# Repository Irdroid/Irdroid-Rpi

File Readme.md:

# Irdroid-Rpi Infrared Transceiver for Raspberry Pi

The latest gadget that we are working on is the Irdroid-Rpi Infrared Transceiver HAT / Add-on board for Raspberry Pi. The board provides Infrared Transmitter , Infrared Receiver and UEXT interconnect for Olimex sensors and boards designed with the UEXT connector. The board can be stacked on top of the Rpi board and you could turn your Rpi into a fully functional Infrared remote control for you home infrared consumer electronics. The Irdroid-Rpi is compatible with the LIRC/ Lirc GPIO driver for raspberry Pi and the LIRC utilities for recording and transmitting infrared signals can be used. The Irdroid-Rpi uses a optical IR amplification technique that allows to transmit high power IR signal by signal amplification after the IR light is emitted.

- Infrared Transceiver add-on / HAT for Raspberry Pi
- Infrared Transmitter @940nm with 10+ meters range
- Infrared Receiver up to 40khz and 10+ meters of receive range
- On-board UEXT Interconnect for connecting Olimex sensors and boards.
- Open Source Hardware.

### Version
1.0

### Installation Instructions

Detailed Installation Instructions https://irdroid.eu/wp-content/uploads/2020/03/Irdroid-Rpi-Installation-Guide.txt

### Grab a sample

You can grab a sample board from http://www.irdroid.eu/irdroid-rpi-infrared-transceiver-raspberry-pi/
### Tech

The Irdroid-Rpi infrared transceiver for Raspberry Pi is also designed with the possibility to connect sensors and boards from Olimex (http://www.olimex.com) by using the on-board UEXT connector, designed by Olimex. You can check here what sensors are supported https://www.olimex.com/Products/Components/Sensors/ .

### Todos

 - Add holders for the infrared leds in schematic
 
### Updates

Irdroid-Rpi now has a DT Overlay support via the on-board eeprom that now ships with every board. Once attached to a Raspberry Pi, the Irdroid-Rpi Hat will be recognized automatically, it will set the board inputs and outputs, and it will load the appropriate Kernel LIRC-RPI drivers. This feature improoves user experience and it provides plug-n-play support for the Product. The user will only have to install lircd (if not shipped by default with the distribution used).

The Irdroid-Rpi board details such as Vendor and Product IDs are available in 

/proc/device-tree/hat

To query Product & Vendor use:

$ more product  

$ more vendor

License
----
GPL 2.0

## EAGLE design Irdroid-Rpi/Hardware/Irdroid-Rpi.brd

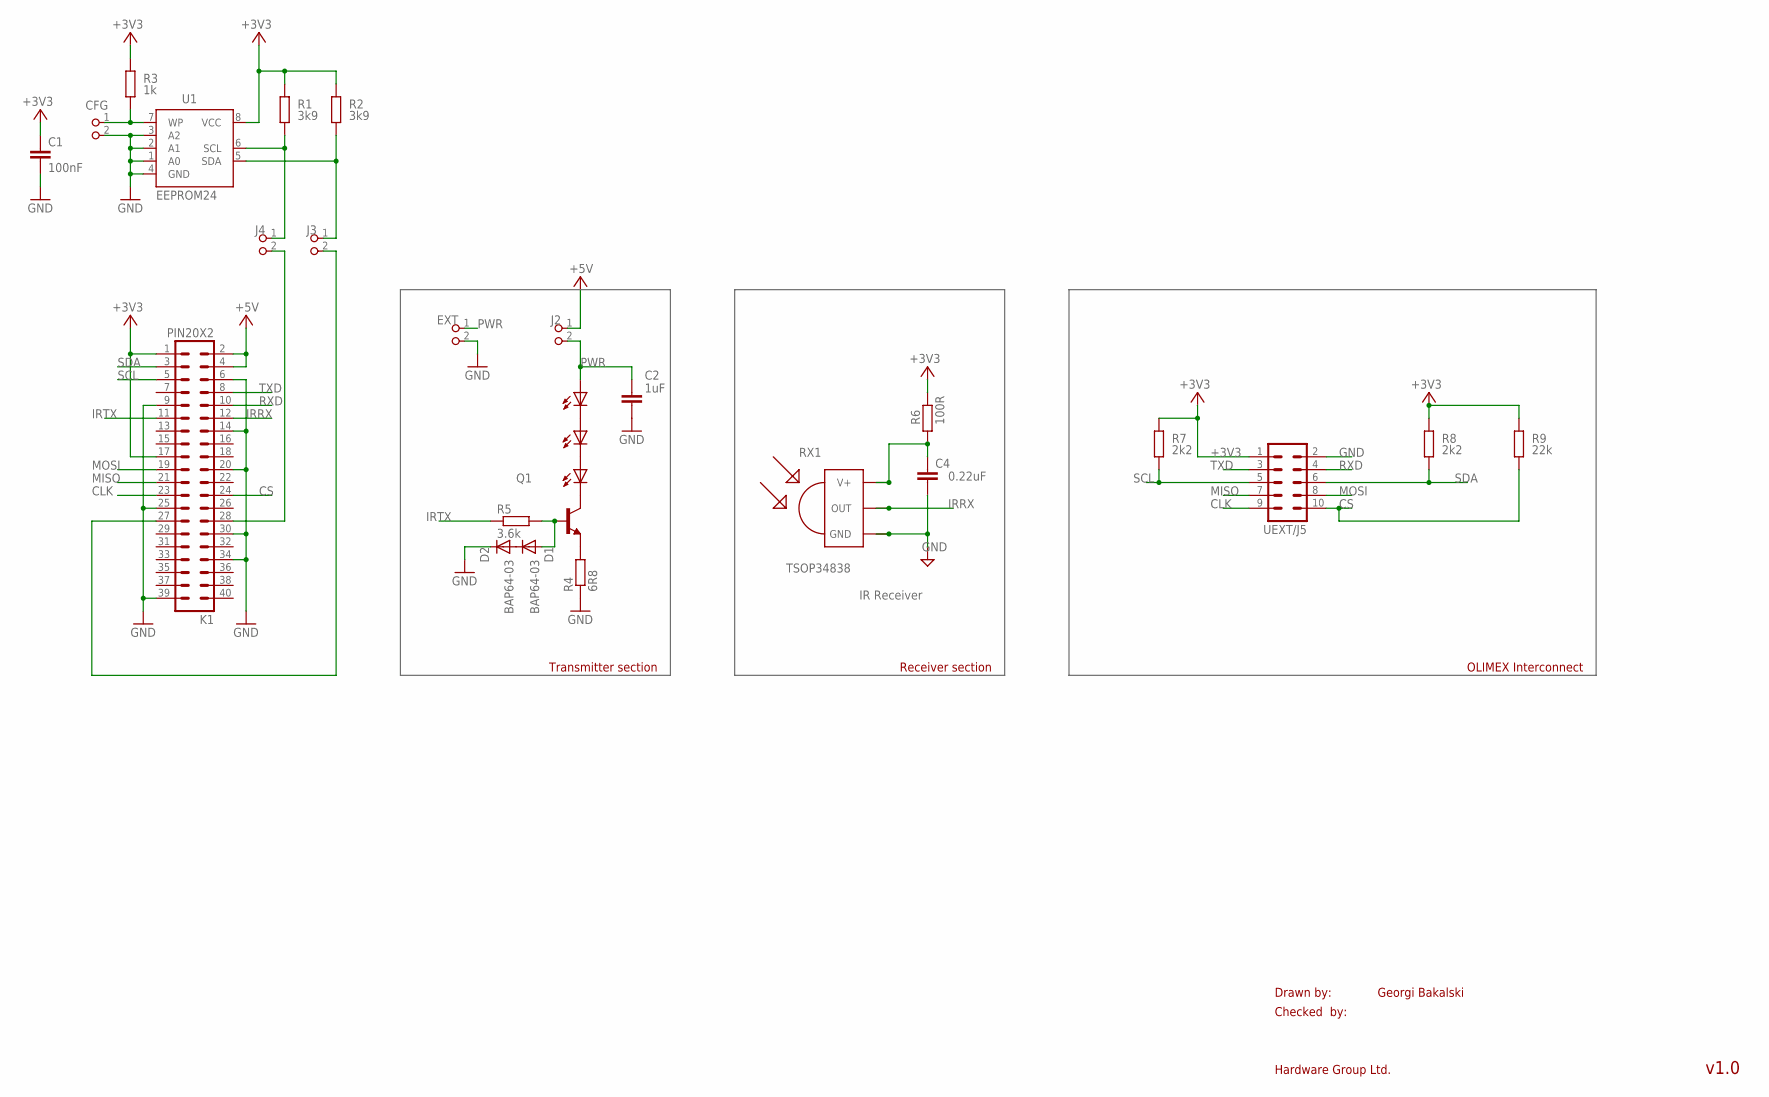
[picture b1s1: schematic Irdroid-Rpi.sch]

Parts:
C1: 100nF; C0805K
C2: 1uF; C603@1
C4: 0.22uF; C603
CFG: PIN2_100; PIN_W_2
D1, D2: BAP64-03; DO323
EXT: PIN2_100; PIN_W_2
J2, J3, J4: PIN2_100; PIN_W_2
K1: PIN20X2; PIN_20X2
Q1: TRANSISTOR_BJT_NPN-SOT-23-BCE; SOT-23
R1, R2: 3k9; M0805; TOLERANCE 5%
R3: 1k; M0805; TOLERANCE 5%
R4: 6R8; R1206
R5: 3.6k; R0603
R6: 100R; R603
R7, R8: 2k2; M0805; TOLERANCE 5%
R9: 22k; M0805; TOLERANCE 5%
RX1: TSOP34838; TSOP18XX
U1: EEPROM24; SOIC8
U$5, U$6, U$7: IRLED5MM; IRLED_HOLDER
UEXT/J5: ML10

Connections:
+3V3: C1.1, K1.1, K1.17, R1.2, R2.2, R3.2, R6.2, R7.2, R8.2, R9.2, U1.8 (VCC), UEXT/J5.1
+5V: J2.1, K1.2, K1.4
CLK: K1.23, UEXT/J5.9
CS: K1.24, R9.1, UEXT/J5.10
GND: C1.2, C2.2, C4.2, CFG.2, D2.C, EXT.2, K1.6, K1.9, K1.14, K1.20, K1.25, K1.30, K1.34, K1.39, R4.1, RX1.GND, U1.1 (A0), U1.2 (A1), U1.3 (A2), U1.4 (GND), UEXT/J5.2
IRRX: K1.12, RX1.OUT
IRTX: K1.11, R5.1
MISO: K1.21, UEXT/J5.7
MOSI: K1.19, UEXT/J5.8
unnamed: J4.2, K1.28
unnamed: J3.2, K1.27
unnamed: CFG.1, R3.1, U1.7 (WP)
unnamed: Q1.3 (E), R4.2
unnamed: Q1.2 (C), U$5.K (C)
unnamed: U$5.A, U$6.K (C)
unnamed: U$6.A, U$7.K (C)
unnamed: D1.A, Q1.1 (B), R5.2
unnamed: D1.C, D2.A
unnamed: C4.1, R6.1, RX1.VCC (V+)
unnamed: J4.1, R1.1, U1.6 (SCL)
unnamed: J3.1, R2.1, U1.5 (SDA)
PWR: C2.1, EXT.1, J2.2, U$7.A
RXD: K1.10, UEXT/J5.4
SCL: K1.5, R7.1, UEXT/J5.5
SDA: K1.3, R8.1, UEXT/J5.6
TXD: K1.8, UEXT/J5.3

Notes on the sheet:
Drawn by:
Checked by:
Hardware Group Ltd.
Georgi Bakalski
v1.0
Transmitter section
RX1
TSOP34838
IR Receiver
Receiver section
OLIMEX Interconnect

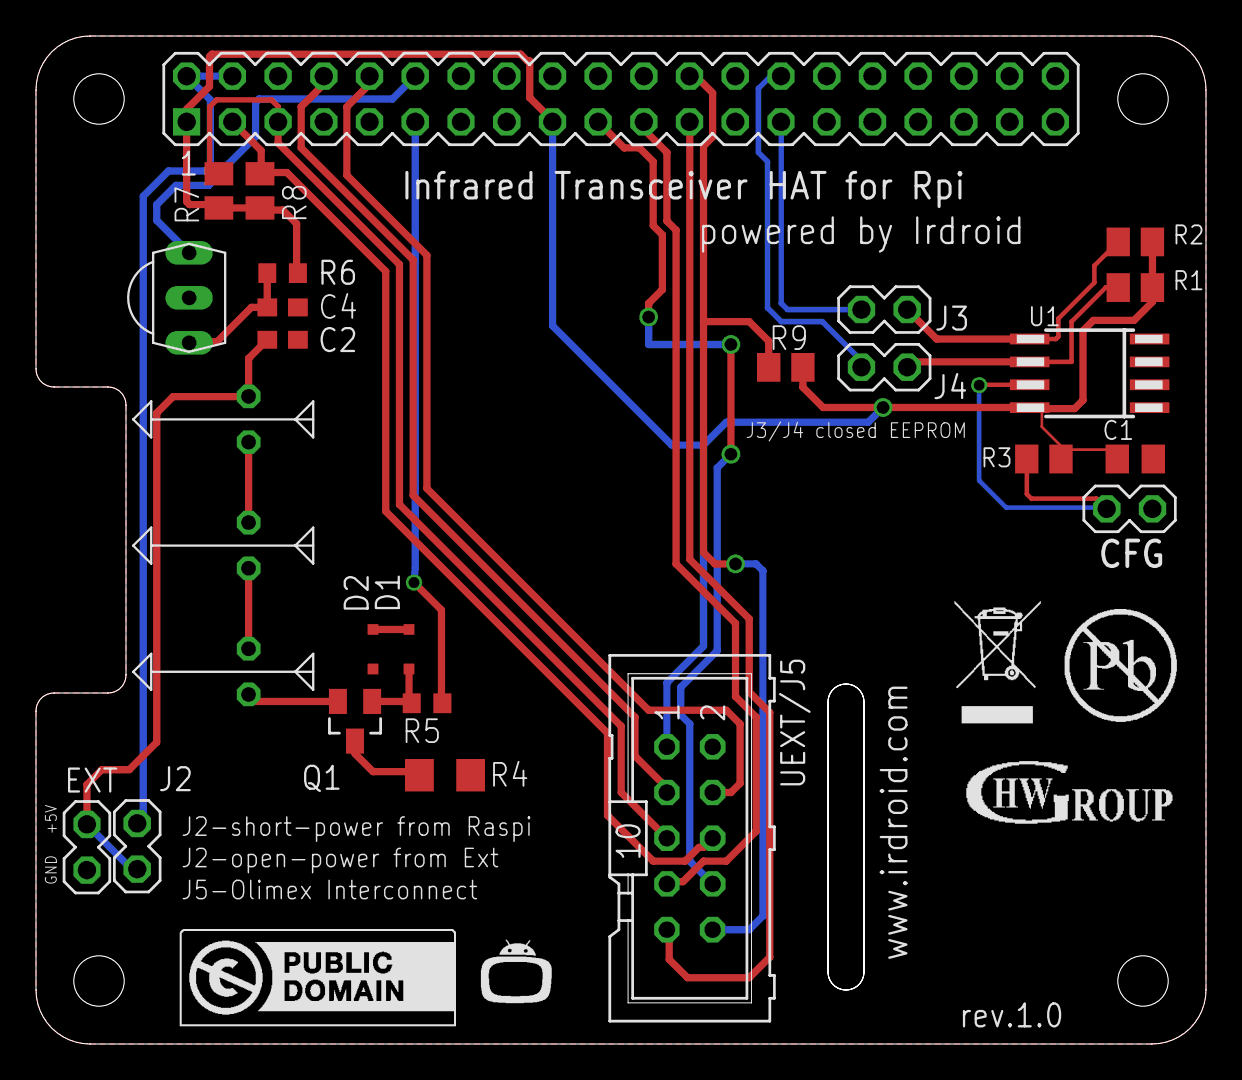
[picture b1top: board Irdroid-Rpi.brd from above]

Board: 2 copper layers, 65.0 x 56.0 mm, 31 parts (0 on the bottom side), 26 nets.

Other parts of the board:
U$1: LOGO_CC-0
U$2: IRDROIDLOGO
U$3: TRASH
U$4: HWGROUP

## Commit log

2016-03-18 Initial Release 1.0
2016-03-18 Added Irdroid-Rpi Schematic and PCB pdf prints
2016-03-18 Added Readme.md in the main folder
2016-03-21 Changed and updated the Infrared LED library with a plastic 90 degrees holder.
2016-03-21 Added board Gerbers
2016-10-18 Updated the Irdroid-Rpi user's Manual / Section configuration for Raspbian
2018-05-25 DeviceTree overlay support via onboard EEPROM
    DeviceTree overlay support via onboard EEPROM
2020-03-25 Updated Readme.md
    Added latest installation instructions for Raspbian
2020-03-25 Update Readme.md
    Updated Readme.md
